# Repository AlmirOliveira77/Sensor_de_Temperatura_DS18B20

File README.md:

# Sensor de Temperatura DS18B20
## Integrantes: 
 - Almir de Oliveira Pereira <br>
 - Gabriel Faustino da Silva <br>
 - Jhônata Vinícius Da Silva Negreiros

## Descrição:

<p align="justify">Simular o controle de temperatura de um reservatório de água. Por meio do uso do microcontrolador ATmega328P, manteremos a temperatura entre 18º e 22º. Ao atingir a temperatura mínima ou máxima do intervalo, um sinal sonoro será emitido pelo buzzer, o que substituiria por um sistema de liga e desliga de uma resistência para manutenção da temperatura de um aquário, por exemplo. Com a utilização de um push button, poderemos criar um "modo silencioso", no qual ao invés do buzzer ser acionado nas circunstâncias específicas, um led vermelho seria acionado. As temperaturas são exibidas em tempo real no display LCD.

A escolha dos componentes do projeto se deu pela necessidade de utilização do Sensor de Temperatura DS18B20, o que nos guiou para a utilização dos mesmos, a fim de atingir com sucesso o uso do sensor na prática desenvolvida para esta disciplina de Técnicas de Prototipagem.

No decorrer do projeto, tivemos a oportunidade conhecer mais na prática os conceitos de prototipagem e sistemas embarcados aplicados por nosso professor. E durante a execução, pudemos perceber algumas dificuldades no que diz respeito ao encontro entre os integrantes do grupo para realização do projeto em si, o que se deve ao fato de estarmos vivenciando momentos nos quais a distância também se dá pela internet e vidas pessoais. Também tivemos algumas dificuldades no desenvolvimento da placa PCB, pois utilizamos um programa recentemente conhecido pelos integrantes do grupo, mas que foi superado com o esforço contínuo e em conjunto de todos.</p>

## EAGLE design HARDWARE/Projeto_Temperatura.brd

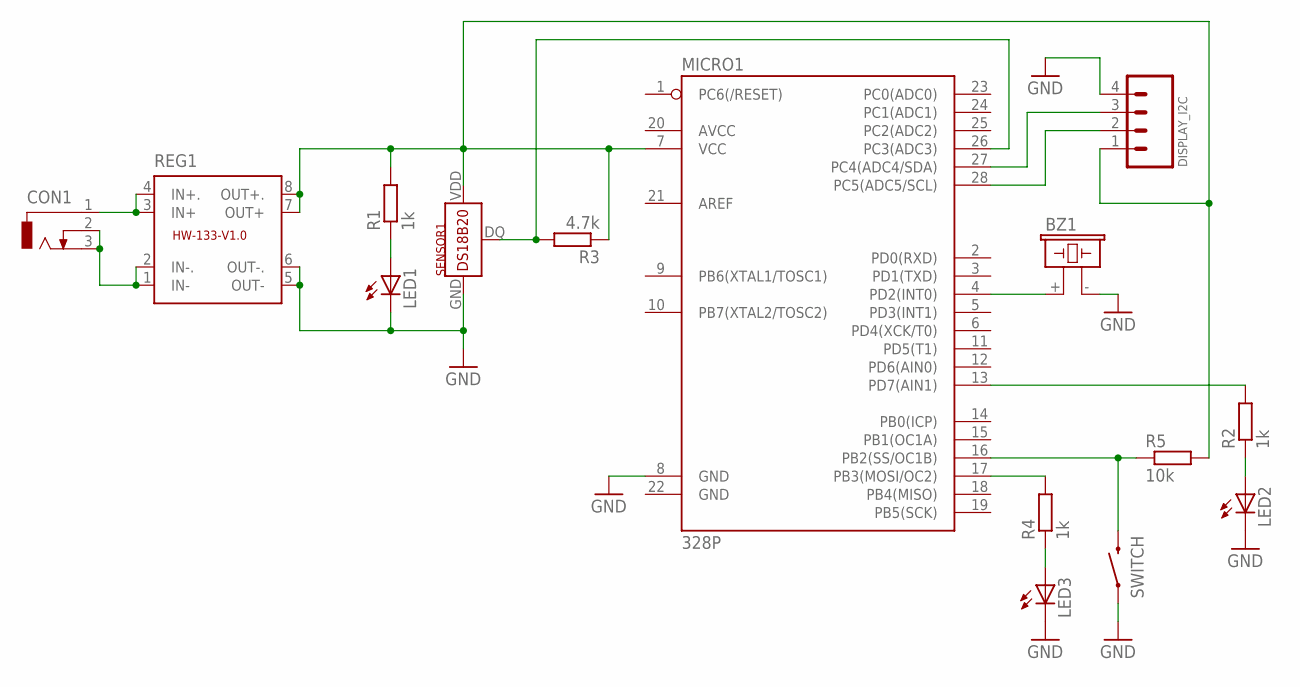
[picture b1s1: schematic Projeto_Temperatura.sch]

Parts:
BZ1: F/CM12P
CON1: DCJ0202
DISPLAY_I2C: MA04; 04PA
LED1, LED2, LED3: LED5MM
MICRO1: 328P; DIP28
R1, R2, R4: 1k; 0204/7
R3: 4.7k; 0204/7
R5: 10k; 0204/7
REG1: REGULADOR
SENSOR1: DS18B20; TO-92
SWITCH: MOMENTARY-SWITCH-SPST-PTH-RIGHT-ANGLE-KIT; TACTILE_SWITCH_PTH_RIGHT_ANGLE_KIT

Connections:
GND: BZ1.- (2), DISPLAY_I2C.4, LED1.K (C), LED2.K (C), LED3.K (C), MICRO1.8 (GND), REG1.5 (OUT-), REG1.6 (OUT-.), SENSOR1.GND (1), SWITCH.1
unnamed: LED2.A, R2.1
unnamed: MICRO1.13 (PD7(AIN1)), R2.2
unnamed: LED1.A, R1.1
unnamed: LED3.A, R4.1
unnamed: MICRO1.26 (PC3(ADC3)), R3.2, SENSOR1.DQ (2)
unnamed: MICRO1.17 (PB3(MOSI/OC2)), R4.2
unnamed: BZ1.+ (1), MICRO1.4 (PD2(INT0))
unnamed: MICRO1.16 (PB2(SS/OC1B)), R5.1, SWITCH.2
unnamed: DISPLAY_I2C.3, MICRO1.27 (PC4(ADC4/SDA))
unnamed: DISPLAY_I2C.2, MICRO1.28 (PC5(ADC5/SCL))
unnamed: DISPLAY_I2C.1, MICRO1.7 (VCC), R1.2, R3.1, R5.2, REG1.7 (OUT+), REG1.8 (OUT+.), SENSOR1.VDD (3)
unnamed: CON1.1, REG1.3 (IN+), REG1.4 (IN+.)
unnamed: CON1.2, CON1.3, REG1.1 (IN-), REG1.2 (IN-.)

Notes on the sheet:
REG1

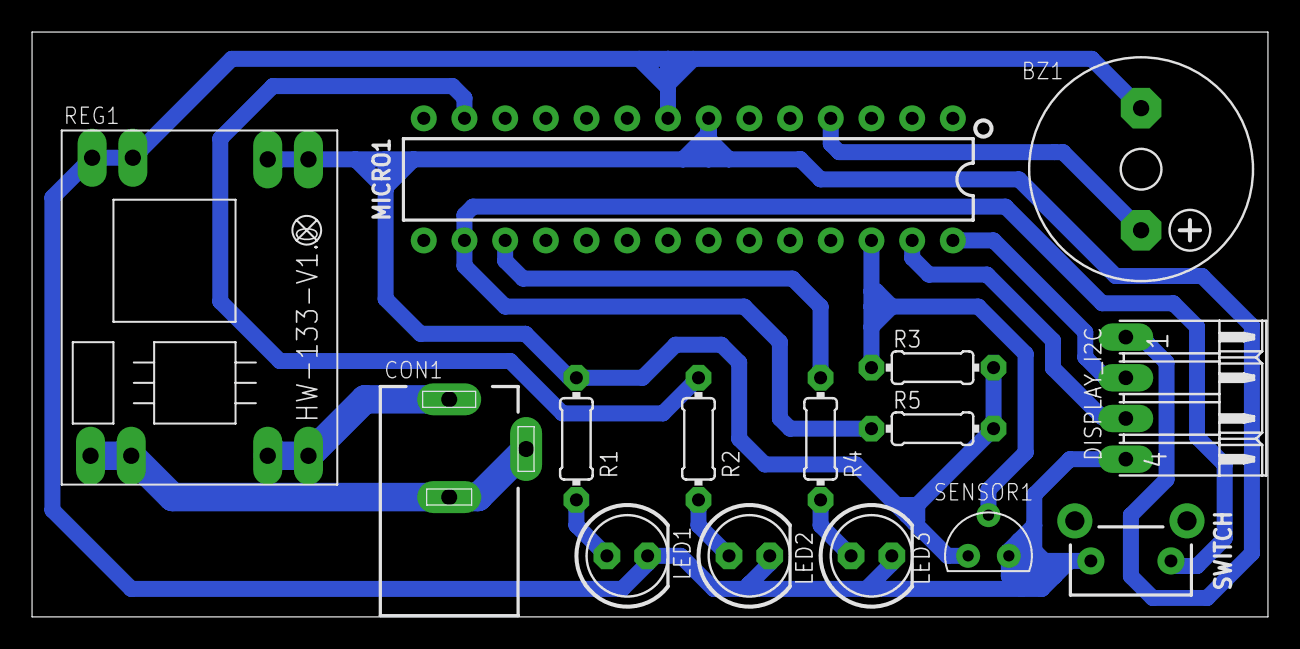
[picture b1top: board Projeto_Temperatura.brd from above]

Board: 2 copper layers, 77.1 x 36.5 mm, 15 parts (0 on the bottom side), 14 nets.

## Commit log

2021-07-28 Create teste2
2021-09-24 Create BOM
2021-09-24 Rename BOM.txt to BOM.md
2021-09-24 Rename ex.txt to Função.md
2021-09-24 Rename Hardware/.ex.txt to HARDWARE/ex.txt
2021-09-25 comimit
2021-10-07 Create reg
2021-10-07 Rename reg to Regulador de Tensão

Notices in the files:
parts and their libraries:
SparkFun-IC-Microcontroller: Licensing: Creative Commons ShareAlike 4.0 International - https://creativecommons.org/licenses/by-sa/4.0
